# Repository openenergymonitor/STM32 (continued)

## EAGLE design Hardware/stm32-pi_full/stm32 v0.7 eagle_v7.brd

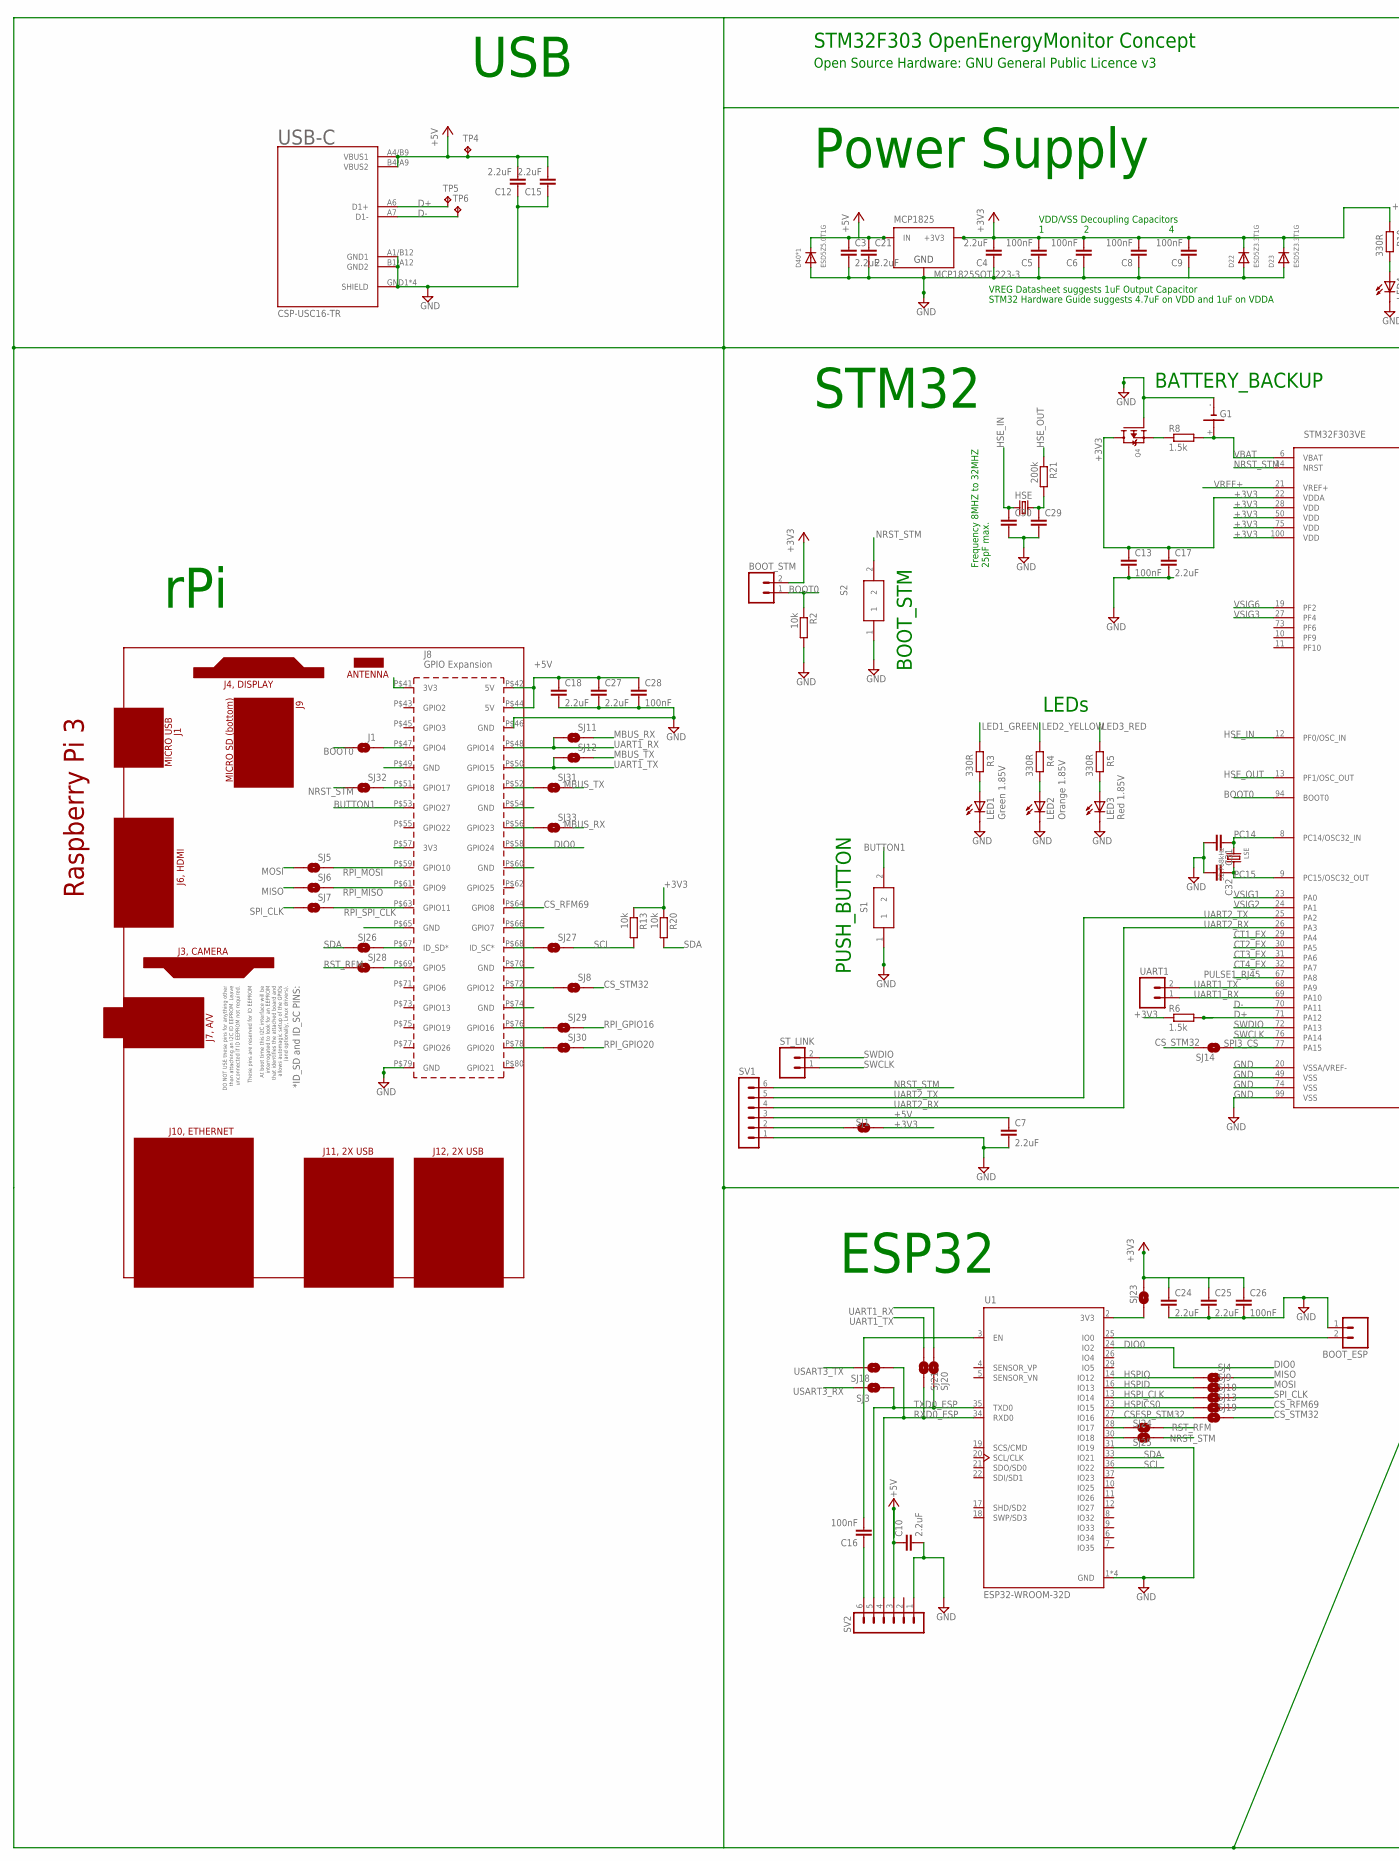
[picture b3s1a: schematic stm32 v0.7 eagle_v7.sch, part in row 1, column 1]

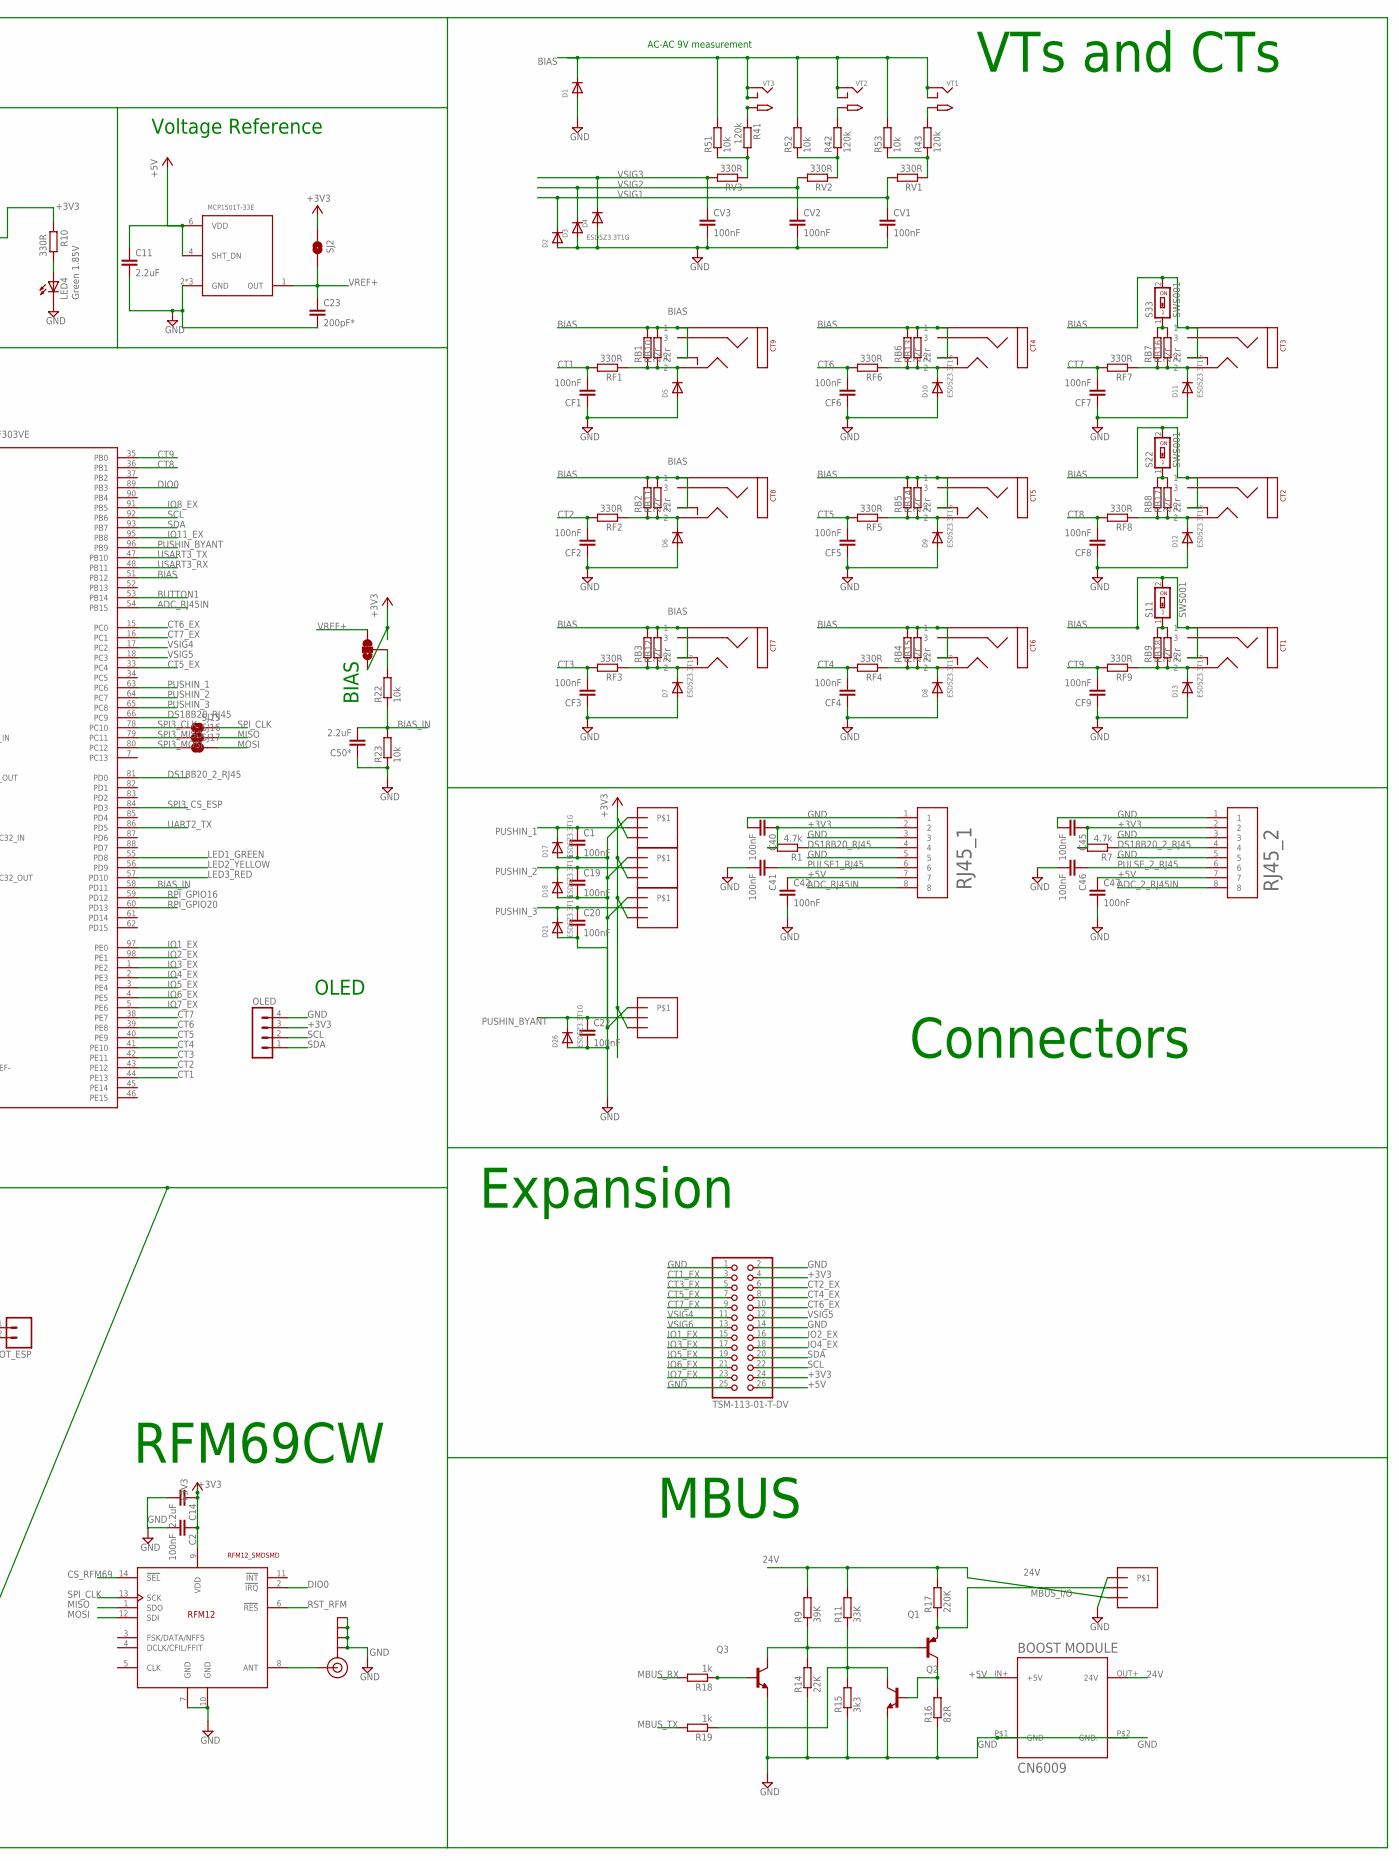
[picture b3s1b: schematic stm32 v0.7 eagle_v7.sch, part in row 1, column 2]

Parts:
BOOT_ESP: M02PTH; 1X02
BOOT_STM: M02PTH; 1X02
C1, C2, C5, C6, C8, C9, C13, C16, C19, C20, C22, C26, C28, C40, C41, C42, C45, C46, C47: 100nF; C0603
C3, C4, C7, C10, C11, C12, C14, C15, C17, C18, C21, C24, C25, C27, C31, C32, C50*: 2.2uF; C0805
C23: 200pF*; C0603
C29, C30: 5nF; C0603
CF1, CF2, CF3, CF4, CF5, CF6, CF7, CF8, CF9: 100nF; C0603
CT1, CT2, CT3, CT4, CT5, CT6, CT7, CT8, CT9: SJ-3523-SMT; STEREO_SMT; MPN SJ-3523-SMT
CV1, CV2, CV3: 100nF; C0603
D1, D2, D3, D4, D5, D6, D7, D8, D9, D10, D11, D12, D13, D17, D18, D21, D22, D23, D26: ESD5Z3.3T1G; SOD-523
D40*1: ESD5Z5.0T1G; SOD-523
EXPANSION: TSM-113-01-T-DV; 2X13_SMT
G1: CH291-1220LF
HSE: 406C35E08M00000; CTS406
J1: SOLDERJUMPERNO; SJ_2S-NO
J$1: SMA_EDGE; SMA-EDGE
JP1: JUMPER-SMT_3_1-NC_TRACE_NO-SILK; SMT-JUMPER_3_1-NC_TRACE_NO-SILK
LED1, LED4: Green 1.85V; CHIP-LED0805
LED2: Orange 1.85V; CHIP-LED0805
LED3: Red 1.85V; CHIP-LED0805
LSE: 32.768kHz; CRYSTAL_8X3.8
MCP1825: MCP1825SOT-223-3; SOT-223
OLED: MA04-1-OLEDOLED; MA04-1-OLED
PCB2: TSM-120-01-T-DV; RPI3MIRROR2
Q1: MMBT3906; SOT23
Q2, Q3: MMBT3904; SOT23
Q4: MOSFET-P; SOT23-R
R1, R7: 4.7k; R0603
R2, R13, R20, R22, R23, R51, R52, R53: 10k; R0603
R3, R4, R5, R10: 330R; R0603
R6, R8: 1.5k; R0603
R9: 39K; R0603
R11: 33K; R0603
R14: 22K; R0603
R15: 3k3; R0603
R16: 82R; R0603
R17: 220K; R0603
R18, R19: 1k; R0603
R21: 200k; R0603
R41, R42, R43: 120k; R0603
RB1, RB2, RB3, RB4, RB5, RB6, RB7, RB8, RB9: 22r; R1206
RB10, RB11, RB12, RB13, RB14, RB15, RB16, RB17, RB18: 22r; 0207/7
RF1, RF2, RF3, RF4, RF5, RF6, RF7, RF8, RF9: 330R; R0603
RFM69HCW: RFM12_SMDSMD; RFM12
RJ45_1, RJ45_2: 95501-6889; 955016889
RV1, RV2, RV3: 330R; R0603
S1, S2: KSS221GLFS; KSS
S11, S22, S33: SWS001; SMS-001
SJ1, SJ2, SJ3, SJ4, SJ5, SJ6, SJ7, SJ8, SJ9, SJ10, SJ11, SJ12, SJ13, SJ14, SJ15, SJ16, SJ17, SJ18, SJ19, SJ20, SJ21, SJ23, SJ24, SJ25, SJ26, SJ27, SJ28, SJ29, SJ30, SJ31, SJ32, SJ33: SOLDERJUMPERNO; SJ_2S-NO
STM32F303VE: STM32F303VE; TQFP100
ST_LINK: M02PTH; 1X02
SV1, SV2: MA06-1
TP4, TP5, TP6: TPB1,27; B1,27
U1: ESP32-WROOM-32D; MODULE_ESP32-WROOM-32D
U$1, U$3, U$4, U$5, U$6: 3.5MM_TERMINAL_BLOCK; 3.5MM_X3
U$2: BOOST_MODULE; BOOST
UART1: M02PTH; 1X02
USB-C: CSP-USC16-TR; USB-C
VREF_3V3: MCP1501T-33E; SOT95P280X145-6N
VT1, VT2, VT3: ADC-028-2-T; DCJACK_2MM_SMT; MPN ADC-028-1-T

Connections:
24V: R9.2, R11.2, R17.2, U$2.OUT+ (24V), U$6.P$1
+3V3: BOOT_STM.2, C2.1, C4.2, C5.2, C6.2, C8.2, C9.2, C13.1, C14.1, C17.1, C24.1, C25.1, C26.1, C40.1, C45.1, D22.K (C), D23.K (C), EXPANSION.4, EXPANSION.24, JP1.1, MCP1825.3 (+3V3), OLED.3, Q4.3 (D), R1.2, R6.1, R7.2, R10.2, R13.1, R20.1, RFM69HCW.9 (VDD), RJ45_1.2, RJ45_2.2, SJ1.2, SJ2.1, SJ23.2, STM32F303VE.22 (VDDA), STM32F303VE.28 (VDD), STM32F303VE.50 (VDD), STM32F303VE.75 (VDD), STM32F303VE.100 (VDD), U$1.P$1, U$3.P$1, U$4.P$1, U$5.P$1
+3V3_ESP: SJ23.1, U1.2 (3V3)
+5V: C3.1, C7.1, C10.1, C11.1, C12.2, C15.2, C18.1, C21.1, C27.1, C28.1, C42.1, C47.1, D40*1.K (C), EXPANSION.26, MCP1825.1 (IN), PCB2.P$42 (5V), PCB2.P$44 (5V), RJ45_1.7, RJ45_2.7, SV1.3, SV2.3, TP4.TP, U$2.IN+ (+5V), USB-C.A4/B9 (VBUS1), USB-C.B4/A9 (VBUS2), VREF_3V3.4 (SHT_DN), VREF_3V3.6 (VDD)
AC1: R43.2, VT1.PWR2 (TIP)
AC2: R42.2, VT2.PWR2 (TIP)
AC3: R41.1, VT3.PWR2 (TIP)
ADC0: R41.2, R51.1, RV3.1
ADC_2_RJ45IN: RJ45_2.8
ADC_RJ45IN: RJ45_1.8, STM32F303VE.54 (PB15)
ANT: J$1.SIG (SIGNAL), RFM69HCW.8 (ANT)
BIAS: CT1.P$1 (1), CT1.P$4 (4), CT2.P$1 (1), CT2.P$4 (4), CT3.P$1 (1), CT3.P$4 (4), CT4.P$1 (1), CT4.P$4 (4), CT5.P$1 (1), CT5.P$4 (4), CT6.P$1 (1), CT6.P$4 (4), CT7.P$1 (1), CT7.P$4 (4), CT8.P$1 (1), CT8.P$4 (4), CT9.P$1 (1), CT9.P$4 (4), D1.K (C), R51.2, R52.2, R53.2, RB1.2, RB2.2, RB3.2, RB4.2, RB5.2, RB6.2, RB10.2, RB11.2, RB12.2, RB13.2, RB14.2, RB15.2, S11.2, S22.2, S33.2, STM32F303VE.51 (PB12), VT1.GND (RING), VT1.GNDBREAK (RING_SW), VT2.GND (RING), VT2.GNDBREAK (RING_SW), VT3.GND (RING), VT3.GNDBREAK (RING_SW)
BIAS_IN: C50*.2, R22.1, R23.2, STM32F303VE.58 (PD11)
BOOT0: BOOT_STM.1, J1.1, R2.1, STM32F303VE.94 (BOOT0)
BOOT0_RPI: J1.2, PCB2.P$47 (GPIO4)
BUTTON1: PCB2.P$53 (GPIO27), S1.2, STM32F303VE.53 (PB14)
CSESP_STM32: SJ19.1, U1.27 (IO16)
CS_RFM69: PCB2.P$64 (GPIO8), RFM69HCW.14 (!SEL), SJ13.2
CS_STM32: SJ8.2, SJ14.1, SJ19.2
CS_STM32_RPI: PCB2.P$72 (GPIO12), SJ8.1
CT1: CF1.2, RF1.2, STM32F303VE.44 (PE13)
CT1_EX: EXPANSION.3, STM32F303VE.29 (PA4)
CT2: CF2.2, RF2.2, STM32F303VE.43 (PE12)
CT2_EX: EXPANSION.6, STM32F303VE.30 (PA5)
CT3: CF3.2, RF3.2, STM32F303VE.42 (PE11)
CT3_EX: EXPANSION.5, STM32F303VE.31 (PA6)
CT4: CF4.2, RF4.2, STM32F303VE.41 (PE10)
CT4_EX: EXPANSION.8, STM32F303VE.32 (PA7)
CT5: CF5.2, RF5.2, STM32F303VE.40 (PE9)
CT5_EX: EXPANSION.7, STM32F303VE.33 (PC4)
CT6: CF6.2, RF6.2, STM32F303VE.39 (PE8)
CT6_EX: EXPANSION.10, STM32F303VE.15 (PC0)
CT7: CF7.2, RF7.2, STM32F303VE.38 (PE7)
CT7_EX: EXPANSION.9, STM32F303VE.16 (PC1)
CT8: CF8.2, RF8.2, STM32F303VE.36 (PB1)
CT9: CF9.2, RF9.2, STM32F303VE.35 (PB0)
D+: R6.2, STM32F303VE.71 (PA12), TP5.TP, USB-C.A6 (D1+)
D-: STM32F303VE.70 (PA11), TP6.TP, USB-C.A7 (D1-)
DIO0: PCB2.P$58 (GPIO24), RFM69HCW.2 (!IRQ), STM32F303VE.89 (PB3), U1.24 (IO2)
DS18B20_2_RJ45: R7.1, RJ45_2.4, STM32F303VE.81 (PD0)
DS18B20_RJ45: R1.1, RJ45_1.4, STM32F303VE.66 (PC9)
GND: BOOT_ESP.1, C1.2, C2.2, C3.2, C4.1, C5.1, C6.1, C7.2, C8.1, C9.1, C10.2, C11.2, C12.1, C13.2, C14.2, C15.1, C17.2, C18.2, C19.2, C20.2, C21.2, C22.2, C23.2, C24.2, C25.2, C26.2, C27.2, C28.2, C29.2, C30.2, C31.2, C32.2, C40.2, C41.2, C42.2, C45.2, C46.2, C47.2, C50*.1, CF1.1, CF2.1, CF3.1, CF4.1, CF5.1, CF6.1, CF7.1, CF8.1, CF9.1, CV1.2, CV2.2, CV3.2, D1.A, D2.A, D3.A, D4.A, D5.A, D6.A, D7.A, D8.A, D9.A, D10.A, D11.A, D12.A, D13.A, D17.A, D18.A, D21.A, D22.A, D23.A, D26.A, D40*1.A, EXPANSION.1, EXPANSION.2, EXPANSION.14, EXPANSION.25, G1.-, J$1.GND@0 (GND), J$1.GND@1 (GND), J$1.GND@2 (GND), J$1.GND@3 (GND), LED1.C, LED2.C, LED3.C, LED4.C, MCP1825.2 (GND), MCP1825.4 (GND), OLED.4, PCB2.P$46 (GND), PCB2.P$49 (GND), PCB2.P$54 (GND), PCB2.P$60 (GND), PCB2.P$65 (GND), PCB2.P$70 (GND), PCB2.P$74 (GND), PCB2.P$79 (GND), Q2.2 (E), Q3.2 (E), Q4.1 (G), R2.2, R14.1, R15.1, R16.1, R23.1, RFM69HCW.7 (GND), RFM69HCW.10 (GND), RJ45_1.1, RJ45_1.3, RJ45_1.5, RJ45_2.1, RJ45_2.3, RJ45_2.5, S1.1, S2.1, STM32F303VE.20 (VSSA/VREF-), STM32F303VE.49 (VSS), STM32F303VE.74 (VSS), STM32F303VE.99 (VSS), SV1.1, SV2.1, U1.1 (GND), U1.15 (GND), U1.31 (IO19), U1.38 (GND), U1.39 (GND), U$1.P$3, U$2.P$1 (GND), U$2.P$2 (GND.), U$3.P$3, U$4.P$3, U$5.P$3, U$6.P$3, USB-C.A1/B12 (GND1), USB-C.B1/A12 (GND2), USB-C.GND1 (SHIELD), USB-C.GND2 (SHIELD), USB-C.GND3 (SHIELD), USB-C.GND4 (SHIELD), VREF_3V3.2 (GND), VREF_3V3.3 (GND), VREF_3V3.5 (GND)
HSE_IN: C30.1, HSE.1, STM32F303VE.12 (PF0/OSC_IN)
HSE_OUT: R21.1, STM32F303VE.13 (PF1/OSC_OUT)
HSE_OUT_: C29.1, HSE.3 (2), R21.2
HSPICS0: SJ13.1, U1.23 (IO15)
HSPID: SJ9.1, U1.16 (IO13)
HSPIQ: SJ4.1, U1.14 (IO12)
HSPI_CLK: SJ10.1, U1.13 (IO14)
IO1_EX: EXPANSION.15, STM32F303VE.97 (PE0)
IO2_EX: EXPANSION.16, STM32F303VE.98 (PE1)
IO3_EX: EXPANSION.17, STM32F303VE.1 (PE2)
IO4_EX: EXPANSION.18, STM32F303VE.2 (PE3)
IO5_EX: EXPANSION.19, STM32F303VE.3 (PE4)
IO6_EX: EXPANSION.21, STM32F303VE.4 (PE5)
IO7_EX: EXPANSION.23, STM32F303VE.5 (PE6)
IO8_EX: STM32F303VE.91 (PB5)
IO11_EX: STM32F303VE.95 (PB8)
LED1_GREEN: R3.2, STM32F303VE.55 (PD8)
LED2_YELLOW: R4.2, STM32F303VE.56 (PD9)
LED3_RED: R5.2, STM32F303VE.57 (PD10)
MBUS_I/O: Q1.2 (E), R17.1, U$6.P$2
MBUS_RX: R18.2, SJ11.2, SJ33.2
MBUS_RX_RPI: PCB2.P$56 (GPIO23), SJ33.1
MBUS_TX: R19.2, SJ12.2, SJ31.2
MBUS_TX_RPI: PCB2.P$52 (GPIO18), SJ31.1
MISO: RFM69HCW.1 (SDO), SJ4.2, SJ6.1, SJ16.2
MOSI: RFM69HCW.12 (SDI), SJ5.1, SJ9.2, SJ17.2
unnamed: SJ1.1, SV1.2
unnamed: CT9.P$2 (2), D5.K (C), RB1.1, RB10.1, RF1.1
unnamed: LED2.A, R4.1
unnamed: LED3.A, R5.1
unnamed: CT8.P$2 (2), D6.K (C), RB2.1, RB11.1, RF2.1
unnamed: LED4.A, R10.1
unnamed: CT7.P$2 (2), D7.K (C), RB3.1, RB12.1, RF3.1
unnamed: JP1.2, R22.2
unnamed: C16.1, SV2.6
unnamed: C16.2, U1.3 (EN)
unnamed: Q4.2 (S), R8.1
unnamed: BOOT_ESP.2, U1.25 (IO0)
unnamed: RB9.2, RB18.2, S11.1
unnamed: RB8.2, RB17.2, S22.1
unnamed: RB7.2, RB16.2, S33.1
unnamed: Q1.3 (C), Q2.1 (B), R16.2
unnamed: Q1.1 (B), Q3.3 (C), R9.1, R14.2
unnamed: Q2.3 (C), R11.1, R15.2, R19.1
unnamed: Q3.1 (B), R18.1
unnamed: R42.1, R52.1, RV2.1
unnamed: R43.1, R53.1, RV1.1
unnamed: CT6.P$2 (2), D8.K (C), RB4.1, RB15.1, RF4.1
unnamed: CT5.P$2 (2), D9.K (C), RB5.1, RB14.1, RF5.1
unnamed: CT4.P$2 (2), D10.K (C), RB6.1, RB13.1, RF6.1
unnamed: LED1.A, R3.1
unnamed: CT3.P$2 (2), D11.K (C), RB7.1, RB16.1, RF7.1
unnamed: CT2.P$2 (2), D12.K (C), RB8.1, RB17.1, RF8.1
unnamed: CT1.P$2 (2), D13.K (C), RB9.1, RB18.1, RF9.1
NRST_STM: S2.2, SJ25.2, SJ32.1, STM32F303VE.14 (NRST), SV1.6
NRST_STM_ESP: SJ25.1, U1.30 (IO18)
NRST_STM_RPI: PCB2.P$51 (GPIO17), SJ32.2
PC14: C31.1, LSE.P$1 (1), STM32F303VE.8 (PC14/OSC32_IN)
PC15: C32.1, LSE.P$4 (2), STM32F303VE.9 (PC15/OSC32_OUT)
PULSE1_RJ45: C41.1, RJ45_1.6, STM32F303VE.67 (PA8)
PULSE_2_RJ45: C46.1, RJ45_2.6
PUSHIN_1: C1.1, D17.K (C), STM32F303VE.63 (PC6), U$1.P$2
PUSHIN_2: C19.1, D18.K (C), STM32F303VE.64 (PC7), U$3.P$2
PUSHIN_3: C20.1, D21.K (C), STM32F303VE.65 (PC8), U$4.P$2
PUSHIN_BYANT: C22.1, D26.K (C), STM32F303VE.96 (PB9), U$5.P$2
RPI_GPIO16: SJ29.2, STM32F303VE.59 (PD12)
RPI_GPIO16_RPI: PCB2.P$76 (GPIO16), SJ29.1
RPI_GPIO20: SJ30.2, STM32F303VE.60 (PD13)
RPI_GPIO20_RPI: PCB2.P$78 (GPIO20), SJ30.1
RPI_MISO: PCB2.P$61 (GPIO9), SJ6.2
RPI_MOSI: PCB2.P$59 (GPIO10), SJ5.2
RPI_SPI_CLK: PCB2.P$63 (GPIO11), SJ7.2
RST_RFM: RFM69HCW.6 (!RES), SJ24.2, SJ28.1
RST_RFM_ESP: SJ24.1, U1.28 (IO17)
RST_RFM_RPI: PCB2.P$69 (GPIO5), SJ28.2
RXD0_ESP: SJ18.1, SJ21.2, SV2.4, U1.34 (RXD0)
SCL: EXPANSION.22, OLED.2, R13.2, SJ27.2, STM32F303VE.92 (PB6), U1.36 (IO22)
SCL_RPI: PCB2.P$68 (ID_SC*), SJ27.1
SDA: EXPANSION.20, OLED.1, R20.2, SJ26.1, STM32F303VE.93 (PB7), U1.33 (IO21)
SDA_RPI: PCB2.P$67 (ID_SD*), SJ26.2
SPI3_CLK: SJ15.1, STM32F303VE.78 (PC10)
SPI3_CS: SJ14.2, STM32F303VE.77 (PA15)
SPI3_CS_ESP: STM32F303VE.84 (PD3)
SPI3_MISO: SJ16.1, STM32F303VE.79 (PC11)
SPI3_MOSI: SJ17.1, STM32F303VE.80 (PC12)
SPI_CLK: RFM69HCW.13 (SCK), SJ7.1, SJ10.2, SJ15.2
SWCLK: STM32F303VE.76 (PA14), ST_LINK.1
SWDIO: STM32F303VE.72 (PA13), ST_LINK.2
TXD0_ESP: SJ3.1, SJ20.2, SV2.5, U1.35 (TXD0)
UART1_RX: PCB2.P$48 (GPIO14), SJ11.1, SJ20.1, STM32F303VE.69 (PA10), UART1.1
UART1_TX: PCB2.P$50 (GPIO15), SJ12.1, SJ21.1, STM32F303VE.68 (PA9), UART1.2
UART2_RX: STM32F303VE.26 (PA3), SV1.4
UART2_TX: STM32F303VE.25 (PA2), STM32F303VE.86 (PD5), SV1.5
USART3_RX: SJ3.2, STM32F303VE.48 (PB11)
USART3_TX: SJ18.2, STM32F303VE.47 (PB10)
VBAT: G1.+, R8.2, STM32F303VE.6 (VBAT)
VREF+: C23.1, JP1.3, SJ2.2, STM32F303VE.21 (VREF+), VREF_3V3.1 (OUT)
VSIG1: CV1.1, D2.K (C), RV1.2, STM32F303VE.23 (PA0)
VSIG2: CV2.1, D3.K (C), RV2.2, STM32F303VE.24 (PA1)
VSIG3: CV3.1, D4.K (C), RV3.2, STM32F303VE.27 (PF4)
VSIG4: EXPANSION.11, STM32F303VE.17 (PC2)
VSIG5: EXPANSION.12, STM32F303VE.18 (PC3)
VSIG6: EXPANSION.13, STM32F303VE.19 (PF2)

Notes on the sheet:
VDD/VSS Decoupling Capacitors
VREG Datasheet suggests 1uF Output Capacitor
STM32 Hardware Guide suggests 4.7uF on VDD and 1uF on VDDA
AC-AC 9V measurement
VTs and CTs
STM32F303 OpenEnergyMonitor Concept
Power Supply
STM32
Open Source Hardware: GNU General Public Licence v3
Frequency 8MHZ to 32MHZ 25pF max.
Voltage Reference
ESP32
MBUS
rPi
BOOT_STM
RFM69CW
Connectors
Expansion
LEDs
PUSH_BUTTON
OLED
BIAS
USB
BATTERY_BACKUP

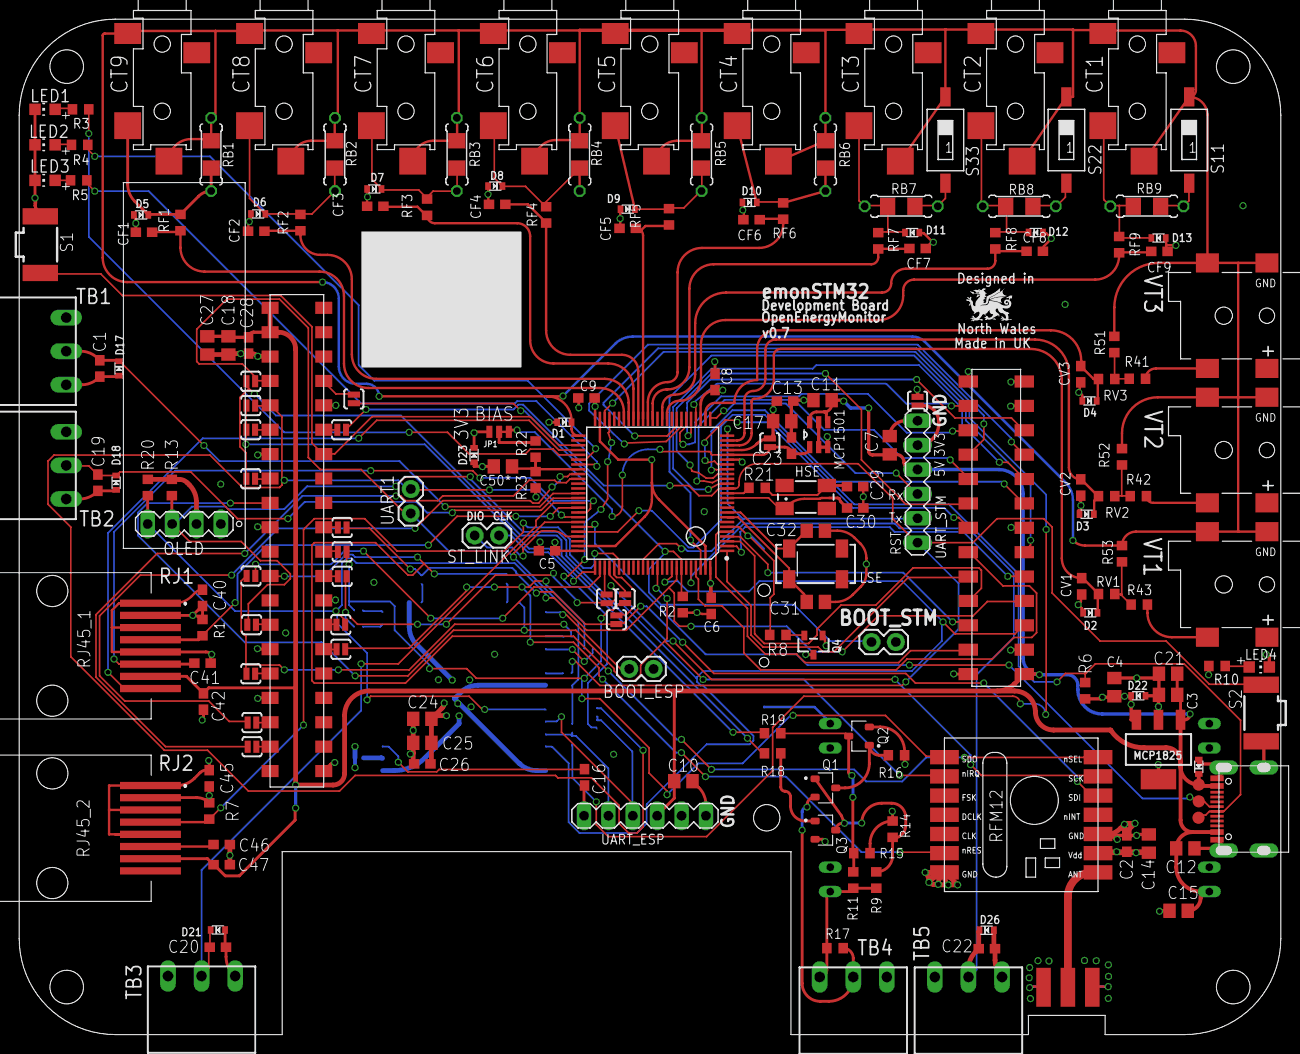
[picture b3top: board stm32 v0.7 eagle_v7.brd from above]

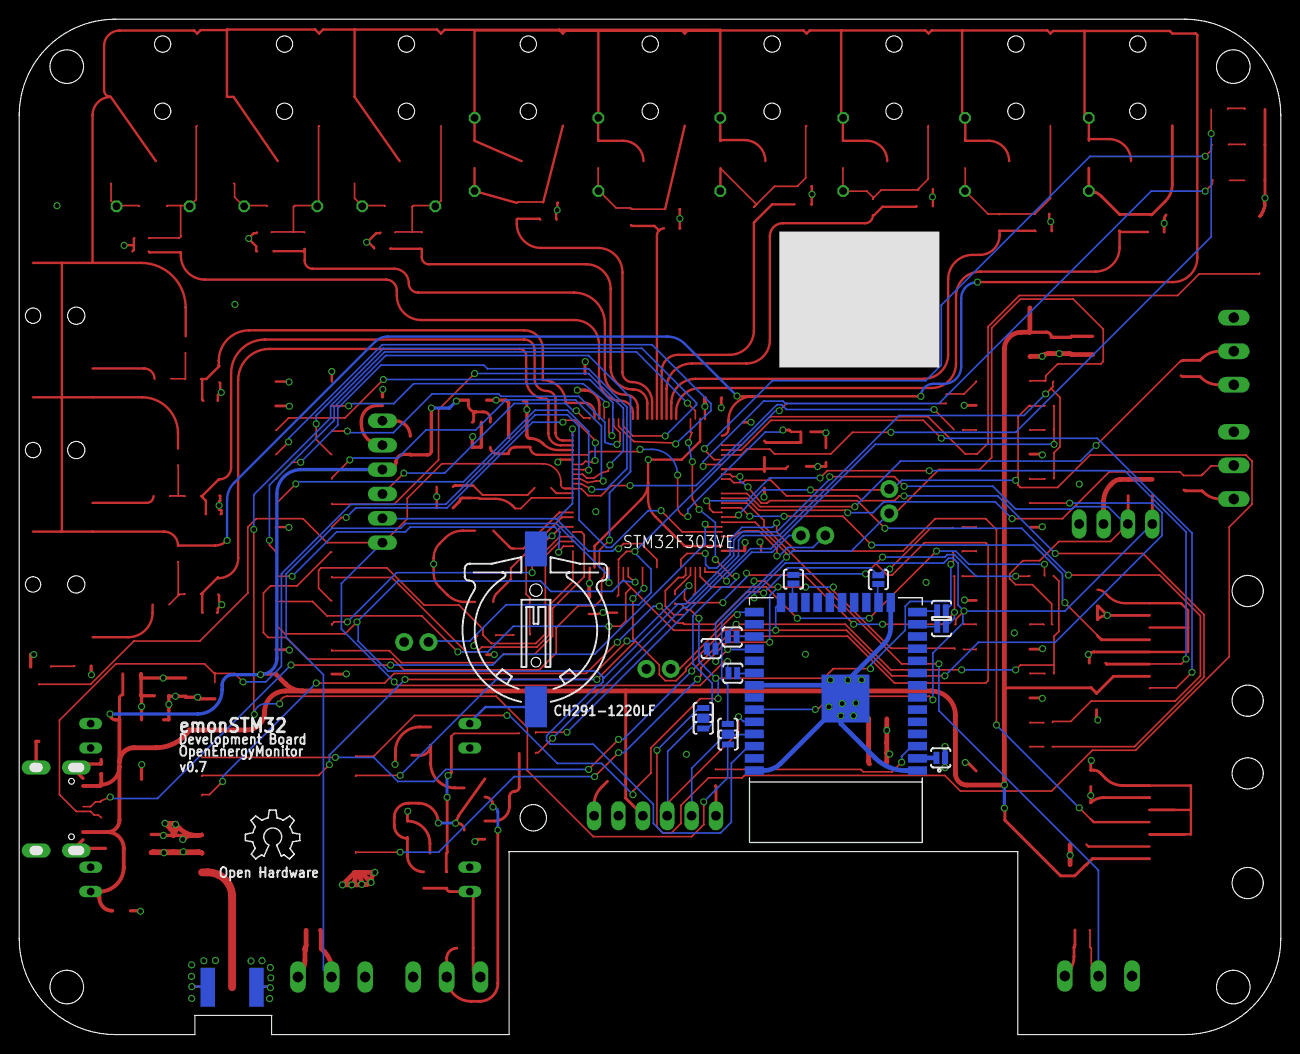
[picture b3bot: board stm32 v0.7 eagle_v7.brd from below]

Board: 4 copper layers, 131.4 x 105.8 mm, 219 parts (15 on the bottom side), 141 nets.

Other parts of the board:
LOGO1: OSHW_LOGO_6MILX0200-NT; OSHW_6X200_NOTEXT

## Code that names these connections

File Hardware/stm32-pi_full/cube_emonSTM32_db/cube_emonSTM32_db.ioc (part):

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Mcu.Name=STM32F303V(B-C)Tx
Mcu.Package=LQFP100
Mcu.UserName=STM32F303VCTx
PA0.Mode=IN1-Single-Ended
PA0.Signal=ADC1_IN1
PA1.Mode=IN2-Single-Ended
PA1.Signal=ADC1_IN2
PA10.Mode=Asynchronous
PA10.Signal=USART1_RX
PA11.Mode=Device
PA11.Signal=USB_DM
PA12.Mode=Device
PA12.Signal=USB_DP
PA13.Mode=Serial_Wire
PA13.Signal=SYS_JTMS-SWDIO
PA14.Mode=Serial_Wire
PA14.Signal=SYS_JTCK-SWCLK
PA15.Mode=NSS_Signal_Hard_Output
PA15.Signal=SPI3_NSS
PA2.Mode=IN3-Single-Ended
PA2.Signal=ADC1_IN3
PA3.Mode=Asynchronous
PA3.Signal=USART2_RX
PA4.Mode=IN1-Single-Ended
PA4.Signal=ADC2_IN1
PA5.Mode=IN2-Single-Ended
PA5.Signal=ADC2_IN2
PA6.Mode=IN3-Single-Ended
PA6.Signal=ADC2_IN3
PA7.Mode=IN4-Single-Ended
PA7.Signal=ADC2_IN4
PA8.GPIOParameters=GPIO_Label
PA8.GPIO_Label=PULSE1_RJ45
PA8.Signal=GPIO_Input
PA9.Mode=Asynchronous
PA9.Signal=USART1_TX
PB0.Mode=IN12-Single-Ended
PB0.Signal=ADC3_IN12
PB1.Mode=IN1-Single-Ended
PB1.Signal=ADC3_IN1
PB10.Mode=Asynchronous
PB10.Signal=USART3_TX
PB11.Mode=Asynchronous
PB11.Signal=USART3_RX
PB12.Mode=Follower
PB12.Signal=OPAMP4_VOUT
PB14.GPIOParameters=GPIO_Label
PB14.GPIO_Label=BUTTON1
PB14.Signal=GPIO_Input
PB5.GPIOParameters=GPIO_Label
PB5.GPIO_Label=IO8_EX
PB5.Signal=GPIO_Input
PB6.Mode=I2C
PB6.Signal=I2C1_SCL
PB7.Mode=I2C
PB7.Signal=I2C1_SDA
PB8.GPIOParameters=GPIO_Label
PB8.GPIO_Label=IO11_EX
PB8.Signal=GPIO_Input
PB9.GPIOParameters=GPIO_Label
PB9.GPIO_Label=PUSHIN_1
PB9.Signal=GPIO_Input
PC0.Signal=ADCx_IN6
PC1.Signal=ADCx_IN7
PC10.Mode=Full_Duplex_Master
PC10.Signal=SPI3_SCK
PC11.Mode=Full_Duplex_Master
PC11.Signal=SPI3_MISO
PC12.Mode=Full_Duplex_Master
PC12.Signal=SPI3_MOSI
PC14-OSC32_IN.Mode=LSE-External-Oscillator
PC14-OSC32_IN.Signal=RCC_OSC32_IN
PC15-OSC32_OUT.Mode=LSE-External-Oscillator
PC15-OSC32_OUT.Signal=RCC_OSC32_OUT
PC2.Signal=ADCx_IN8
PC3.Signal=ADCx_IN9
PC4.Mode=IN5-Single-Ended
PC4.Signal=ADC2_IN5
PC6.GPIOParameters=GPIO_Label
PC6.GPIO_Label=PUSHIN_3
PC6.Signal=GPIO_Input
PC7.GPIOParameters=GPIO_Label
PC7.GPIO_Label=PUSHIN_4
PC7.Signal=GPIO_Input
PC8.GPIOParameters=GPIO_Label
PC8.GPIO_Label=PULSE2
PC8.Signal=GPIO_Input
PC9.GPIOParameters=GPIO_Label
PC9.GPIO_Label=DS18B20_RJ45
PC9.Signal=GPIO_Input
PD0.Signal=GPIO_Input
PD1.Signal=GPIO_Input
PD10.GPIOParameters=GPIO_Label
PD10.GPIO_Label=LED3
PD10.Signal=GPIO_Output
PD11.Mode=Follower
PD11.Signal=OPAMP4_VINP
PD12.GPIOParameters=GPIO_Label
PD12.GPIO_Label=rpi_gpio16
PD12.Signal=GPIO_Input
PD13.GPIOParameters=GPIO_Label
PD13.GPIO_Label=rpi_gpio20
PD13.Signal=GPIO_Input
PD14.GPIOParameters=GPIO_Label
PD14.GPIO_Label=DS18B20_2
PD14.Signal=GPIO_Input
PD15.GPIOParameters=GPIO_Label
PD15.GPIO_Label=PUSHIN_2
PD15.Signal=GPIO_Input
PD5.Mode=Asynchronous
PD5.Signal=USART2_TX
PD8.GPIOParameters=GPIO_Label
PD8.GPIO_Label=LED1
PD8.Signal=GPIO_Output
PD9.GPIOParameters=GPIO_Label
PD9.GPIO_Label=LED2
PD9.Signal=GPIO_Output
PE0.GPIOParameters=GPIO_Label
PE0.GPIO_Label=IO1_EX
PE0.Signal=GPIO_Output
PE1.GPIOParameters=GPIO_Label
PE1.GPIO_Label=IO2_EX
PE1.Signal=GPIO_Output
PE10.Mode=IN14-Single-Ended
PE10.Signal=ADC3_IN14
PE11.Mode=IN15-Single-Ended
PE11.Signal=ADC3_IN15
PE12.Mode=IN16-Single-Ended
PE12.Signal=ADC3_IN16
PE13.Mode=IN3-Single-Ended
PE13.Signal=ADC3_IN3
PE2.GPIOParameters=GPIO_Label
PE2.GPIO_Label=IO3_EX
PE2.Signal=GPIO_Output
PE3.GPIOParameters=GPIO_Label
PE3.GPIO_Label=IO4_EX
PE3.Signal=GPIO_Input
PE4.GPIOParameters=GPIO_Label
PE4.GPIO_Label=IO5_EX
PE4.Signal=GPIO_Input
PE5.GPIOParameters=GPIO_Label
PE5.GPIO_Label=IO6_EX
PE5.Signal=GPIO_Input
PE6.GPIOParameters=GPIO_Label
PE6.GPIO_Label=IO7_EX
PE6.Signal=GPIO_Input
PE7.Mode=IN13-Single-Ended
PE7.Signal=ADC3_IN13
PE8.Signal=ADCx_IN6P
PE9.Mode=IN2-Single-Ended
PE9.Signal=ADC3_IN2
PF0-OSC_IN.Mode=HSE-External-Oscillator
PF0-OSC_IN.Signal=RCC_OSC_IN
PF1-OSC_OUT.Mode=HSE-External-Oscillator
PF1-OSC_OUT.Signal=RCC_OSC_OUT
PF2.Signal=ADCx_IN10
PF6.Signal=GPIO_Input
RCC.HSEPLLFreq_Value=8000000
RCC.HSE_VALUE=8000000
RCC.SYSCLKFreq_VALUE=48000000
RCC.SYSCLKSourceVirtual=RCC_SYSCLKSOURCE_PLLCLK
board=custom

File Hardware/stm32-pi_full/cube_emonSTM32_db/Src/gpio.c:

/**
  ******************************************************************************
  * File Name          : gpio.c
  * Description        : This file provides code for the configuration
  *                      of all used GPIO pins.
  ******************************************************************************
  * @attention
  *
  * <h2><center>&copy; Copyright (c) 2019 STMicroelectronics.
  * All rights reserved.</center></h2>
  *
  * This software component is licensed by ST under Ultimate Liberty license
  * SLA0044, the "License"; You may not use this file except in compliance with
  * the License. You may obtain a copy of the License at:
  *                             www.st.com/SLA0044
  *
  ******************************************************************************
  */

/* Includes ------------------------------------------------------------------*/
#include "gpio.h"
/* USER CODE BEGIN 0 */

/* USER CODE END 0 */

/*----------------------------------------------------------------------------*/
/* Configure GPIO                                                             */
/*----------------------------------------------------------------------------*/
/* USER CODE BEGIN 1 */

/* USER CODE END 1 */

/** Configure pins as 
        * Analog 
        * Input 
        * Output
        * EVENT_OUT
        * EXTI
        * Free pins are configured automatically as Analog (this feature is enabled through 
        * the Code Generation settings)
*/
void MX_GPIO_Init(void)
{

  GPIO_InitTypeDef GPIO_InitStruct = {0};

  /* GPIO Ports Clock Enable */
  __HAL_RCC_GPIOE_CLK_ENABLE();
  __HAL_RCC_GPIOC_CLK_ENABLE();
  __HAL_RCC_GPIOF_CLK_ENABLE();
  __HAL_RCC_GPIOA_CLK_ENABLE();
  __HAL_RCC_GPIOB_CLK_ENABLE();
  __HAL_RCC_GPIOD_CLK_ENABLE();

  /*Configure GPIO pin Output Level */
  HAL_GPIO_WritePin(GPIOE, IO3_EX_Pin|IO1_EX_Pin|IO2_EX_Pin, GPIO_PIN_RESET);

  /*Configure GPIO pin Output Level */
  HAL_GPIO_WritePin(GPIOD, LED1_Pin|LED2_Pin|LED3_Pin, GPIO_PIN_RESET);

  /*Configure GPIO pins : PEPin PEPin PEPin */
  GPIO_InitStruct.Pin = IO3_EX_Pin|IO1_EX_Pin|IO2_EX_Pin;
  GPIO_InitStruct.Mode = GPIO_MODE_OUTPUT_PP;
  GPIO_InitStruct.Pull = GPIO_NOPULL;
  GPIO_InitStruct.Speed = GPIO_SPEED_FREQ_LOW;
  HAL_GPIO_Init(GPIOE, &GPIO_InitStruct);

  /*Configure GPIO pins : PEPin PEPin PEPin PEPin */
  GPIO_InitStruct.Pin = IO4_EX_Pin|IO5_EX_Pin|IO6_EX_Pin|IO7_EX_Pin;
  GPIO_InitStruct.Mode = GPIO_MODE_INPUT;
  GPIO_InitStruct.Pull = GPIO_NOPULL;
  HAL_GPIO_Init(GPIOE, &GPIO_InitStruct);

  /*Configure GPIO pins : PC13 PC5 */
  GPIO_InitStruct.Pin = GPIO_PIN_13|GPIO_PIN_5;
  GPIO_InitStruct.Mode = GPIO_MODE_ANALOG;
  GPIO_InitStruct.Pull = GPIO_NOPULL;
  HAL_GPIO_Init(GPIOC, &GPIO_InitStruct);

  /*Configure GPIO pins : PF9 PF10 PF4 */
  GPIO_InitStruct.Pin = GPIO_PIN_9|GPIO_PIN_10|GPIO_PIN_4;
  GPIO_InitStruct.Mode = GPIO_MODE_ANALOG;
  GPIO_InitStruct.Pull = GPIO_NOPULL;
  HAL_GPIO_Init(GPIOF, &GPIO_InitStruct);

  /*Configure GPIO pins : PB2 PB13 PB15 PB3 
                           PB4 */
  GPIO_InitStruct.Pin = GPIO_PIN_2|GPIO_PIN_13|GPIO_PIN_15|GPIO_PIN_3 
                          |GPIO_PIN_4;
  GPIO_InitStruct.Mode = GPIO_MODE_ANALOG;
  GPIO_InitStruct.Pull = GPIO_NOPULL;
  HAL_GPIO_Init(GPIOB, &GPIO_InitStruct);

  /*Configure GPIO pins : PE14 PE15 */
  GPIO_InitStruct.Pin = GPIO_PIN_14|GPIO_PIN_15;
  GPIO_InitStruct.Mode = GPIO_MODE_ANALOG;
  GPIO_InitStruct.Pull = GPIO_NOPULL;
  HAL_GPIO_Init(GPIOE, &GPIO_InitStruct);

  /*Configure GPIO pins : PBPin PBPin PBPin PBPin */
  GPIO_InitStruct.Pin = BUTTON1_Pin|IO8_EX_Pin|IO11_EX_Pin|PUSHIN_1_Pin;
  GPIO_InitStruct.Mode = GPIO_MODE_INPUT;
  GPIO_InitStruct.Pull = GPIO_NOPULL;
  HAL_GPIO_Init(GPIOB, &GPIO_InitStruct);

  /*Configure GPIO pins : PDPin PDPin PDPin */
  GPIO_InitStruct.Pin = LED1_Pin|LED2_Pin|LED3_Pin;
  GPIO_InitStruct.Mode = GPIO_MODE_OUTPUT_PP;
  GPIO_InitStruct.Pull = GPIO_NOPULL;
  GPIO_InitStruct.Speed = GPIO_SPEED_FREQ_LOW;
  HAL_GPIO_Init(GPIOD, &GPIO_InitStruct);

  /*Configure GPIO pins : PDPin PDPin PDPin PDPin 
                           PD0 PD1 */
  GPIO_InitStruct.Pin = rpi_gpio16_Pin|rpi_gpio20_Pin|DS18B20_2_Pin|PUSHIN_2_Pin 
                          |GPIO_PIN_0|GPIO_PIN_1;
  GPIO_InitStruct.Mode = GPIO_MODE_INPUT;
  GPIO_InitStruct.Pull = GPIO_NOPULL;
  HAL_GPIO_Init(GPIOD, &GPIO_InitStruct);

  /*Configure GPIO pins : PCPin PCPin PCPin PCPin */
  GPIO_InitStruct.Pin = PUSHIN_3_Pin|PUSHIN_4_Pin|PULSE2_Pin|DS18B20_RJ45_Pin;
  GPIO_InitStruct.Mode = GPIO_MODE_INPUT;
  GPIO_InitStruct.Pull = GPIO_NOPULL;
  HAL_GPIO_Init(GPIOC, &GPIO_InitStruct);

  /*Configure GPIO pin : PtPin */
  GPIO_InitStruct.Pin = PULSE1_RJ45_Pin;
  GPIO_InitStruct.Mode = GPIO_MODE_INPUT;
  GPIO_InitStruct.Pull = GPIO_NOPULL;
  HAL_GPIO_Init(PULSE1_RJ45_GPIO_Port, &GPIO_InitStruct);

  /*Configure GPIO pin : PF6 */
  GPIO_InitStruct.Pin = GPIO_PIN_6;
  GPIO_InitStruct.Mode = GPIO_MODE_INPUT;
  GPIO_InitStruct.Pull = GPIO_NOPULL;
  HAL_GPIO_Init(GPIOF, &GPIO_InitStruct);

  /*Configure GPIO pins : PD2 PD3 PD4 PD6 
                           PD7 */
  GPIO_InitStruct.Pin = GPIO_PIN_2|GPIO_PIN_3|GPIO_PIN_4|GPIO_PIN_6 
                          |GPIO_PIN_7;
  GPIO_InitStruct.Mode = GPIO_MODE_ANALOG;
  GPIO_InitStruct.Pull = GPIO_NOPULL;
  HAL_GPIO_Init(GPIOD, &GPIO_InitStruct);

}

/* USER CODE BEGIN 2 */

/* USER CODE END 2 */

/************************ (C) COPYRIGHT STMicroelectronics *****END OF FILE****/
